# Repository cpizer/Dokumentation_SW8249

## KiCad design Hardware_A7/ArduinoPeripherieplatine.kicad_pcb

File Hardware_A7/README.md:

Diese Hardware ist in der Komponente die im Schaltplan A7 heisst installiert.

R4,R6,C3 mit circuitlab etwa auf 1kHz im timedomain eingestellt. R4
und R6 halbieren die Eingangsspannung von den angenommenen 40V auf
20V. Die negative Halbwelle fliest nur durch R4 und D6. Habe mit
maximal 40V gerechnet. Sind dann nur 70mW. also passt 1/8W
Widerstand. Die positive Halbwelle wird auf die 5V Schiene
geladen. Diese wird jedoch von der 2,5V Spannungsteilerschaltung so
stark belastet, dass auf keinen Fall rückgespeist wird.

Schmitttrigger R3 und R5 sind dimensioniert auf 3V ein, 2V
aus. Achtung, die OP-AMPS sind im nicht rail to rail!

teste dass der schmitt trigger ausreichend sicher an geht in den
extremlagen wiel die opamps ja nicht rail to rail sind. wenn nicht,
vergrößere R5.

Ohne R6 kann "Signal Licht" frei floaten. Der Widerstand verhindert
das.

D1 ist interessant, wenn die Versorgungsspannung fehlt. Man kann die
Versorgungsspannung jedoch nicht überhöhen, dagegen schützt D5.

D2 gibt die parasitäre Versorgung dann nach aussen weiter und schützt
U1.

C3 ist so dimensioniert dass 1 kHz Grenzfrequenz überschritten
werden. Weil das Original Arduino Programm mit der millis funktion die
Geschwindigkeiten bestimmt und diese maximal 1kHz aufgelöst sein kann.

R1 und R2 sind ein Spannungsteiler zur Erzeugung von 2,5V. Sie dienen
aber auch einer Grundlast um die parasitäre Erzeugung von 5V zu
unterbinden.

R7 ist der Stromshunt für den Kardansensor. Der Kardansensor soll 7mA
oder 14mA liefern. Also ist der Trennpunkt bei 10,5mA. Die Spannung
soll dabei 2,5V sein. Der nächste Widerstand ist dann 220Ohm. R7 soll
wenn er 12V direkt bekommt nicht durchbrennen. 654mW wäre
theoretisch. Daher ein 1W Widerstand. R8 und C6 sind ein
Tiefpass. Wieder eingestellt auf 1kHz Grenzfrequenz.

Auslegung des Schmitt Triggers U4D: 7mA bei 220 Ohm sind 1,54V. 14mA
bei 220 Ohm sind 3,08V. Den Bereich dazwischen dritteln ergibt die
zwei Schranken 2,05V und 2,57V. Mit dem Onlinetool berechnet:
R10=10k R9=1,5k

VD ist die spannung der mitte des 5V opamp ausgangs. also 0-3,5V also
1,75V. mit realen widerständen ist sie 1,85V

https://www.aaabbb.de/NonInvertingSchmittTrigger/NonInvertingSchmittTrigger_en.php

Bedenke den Stromverbrauch des Servos! Er kann die 5V
runterziehen. Mit dem alten defekten Servo der sich nicht mehr drehte
war die 5V Spannung auf 2,6V oder so zusammengebrochen und der Wandler
wurde heiss. Max Servostrom (des neuen nicht defekten Servos) ist
ca. 200mA. der 5V Linear Wandler wird nach einer Minute Servo
dauerlauf hot und regelt runter. Ist auch logisch bei 24V input. Habe
daher den Servopower entkoppelt mit einem Schaltregler.

Die Drehzahlanzeige hat einen Widerstand von 2,5kOhm.

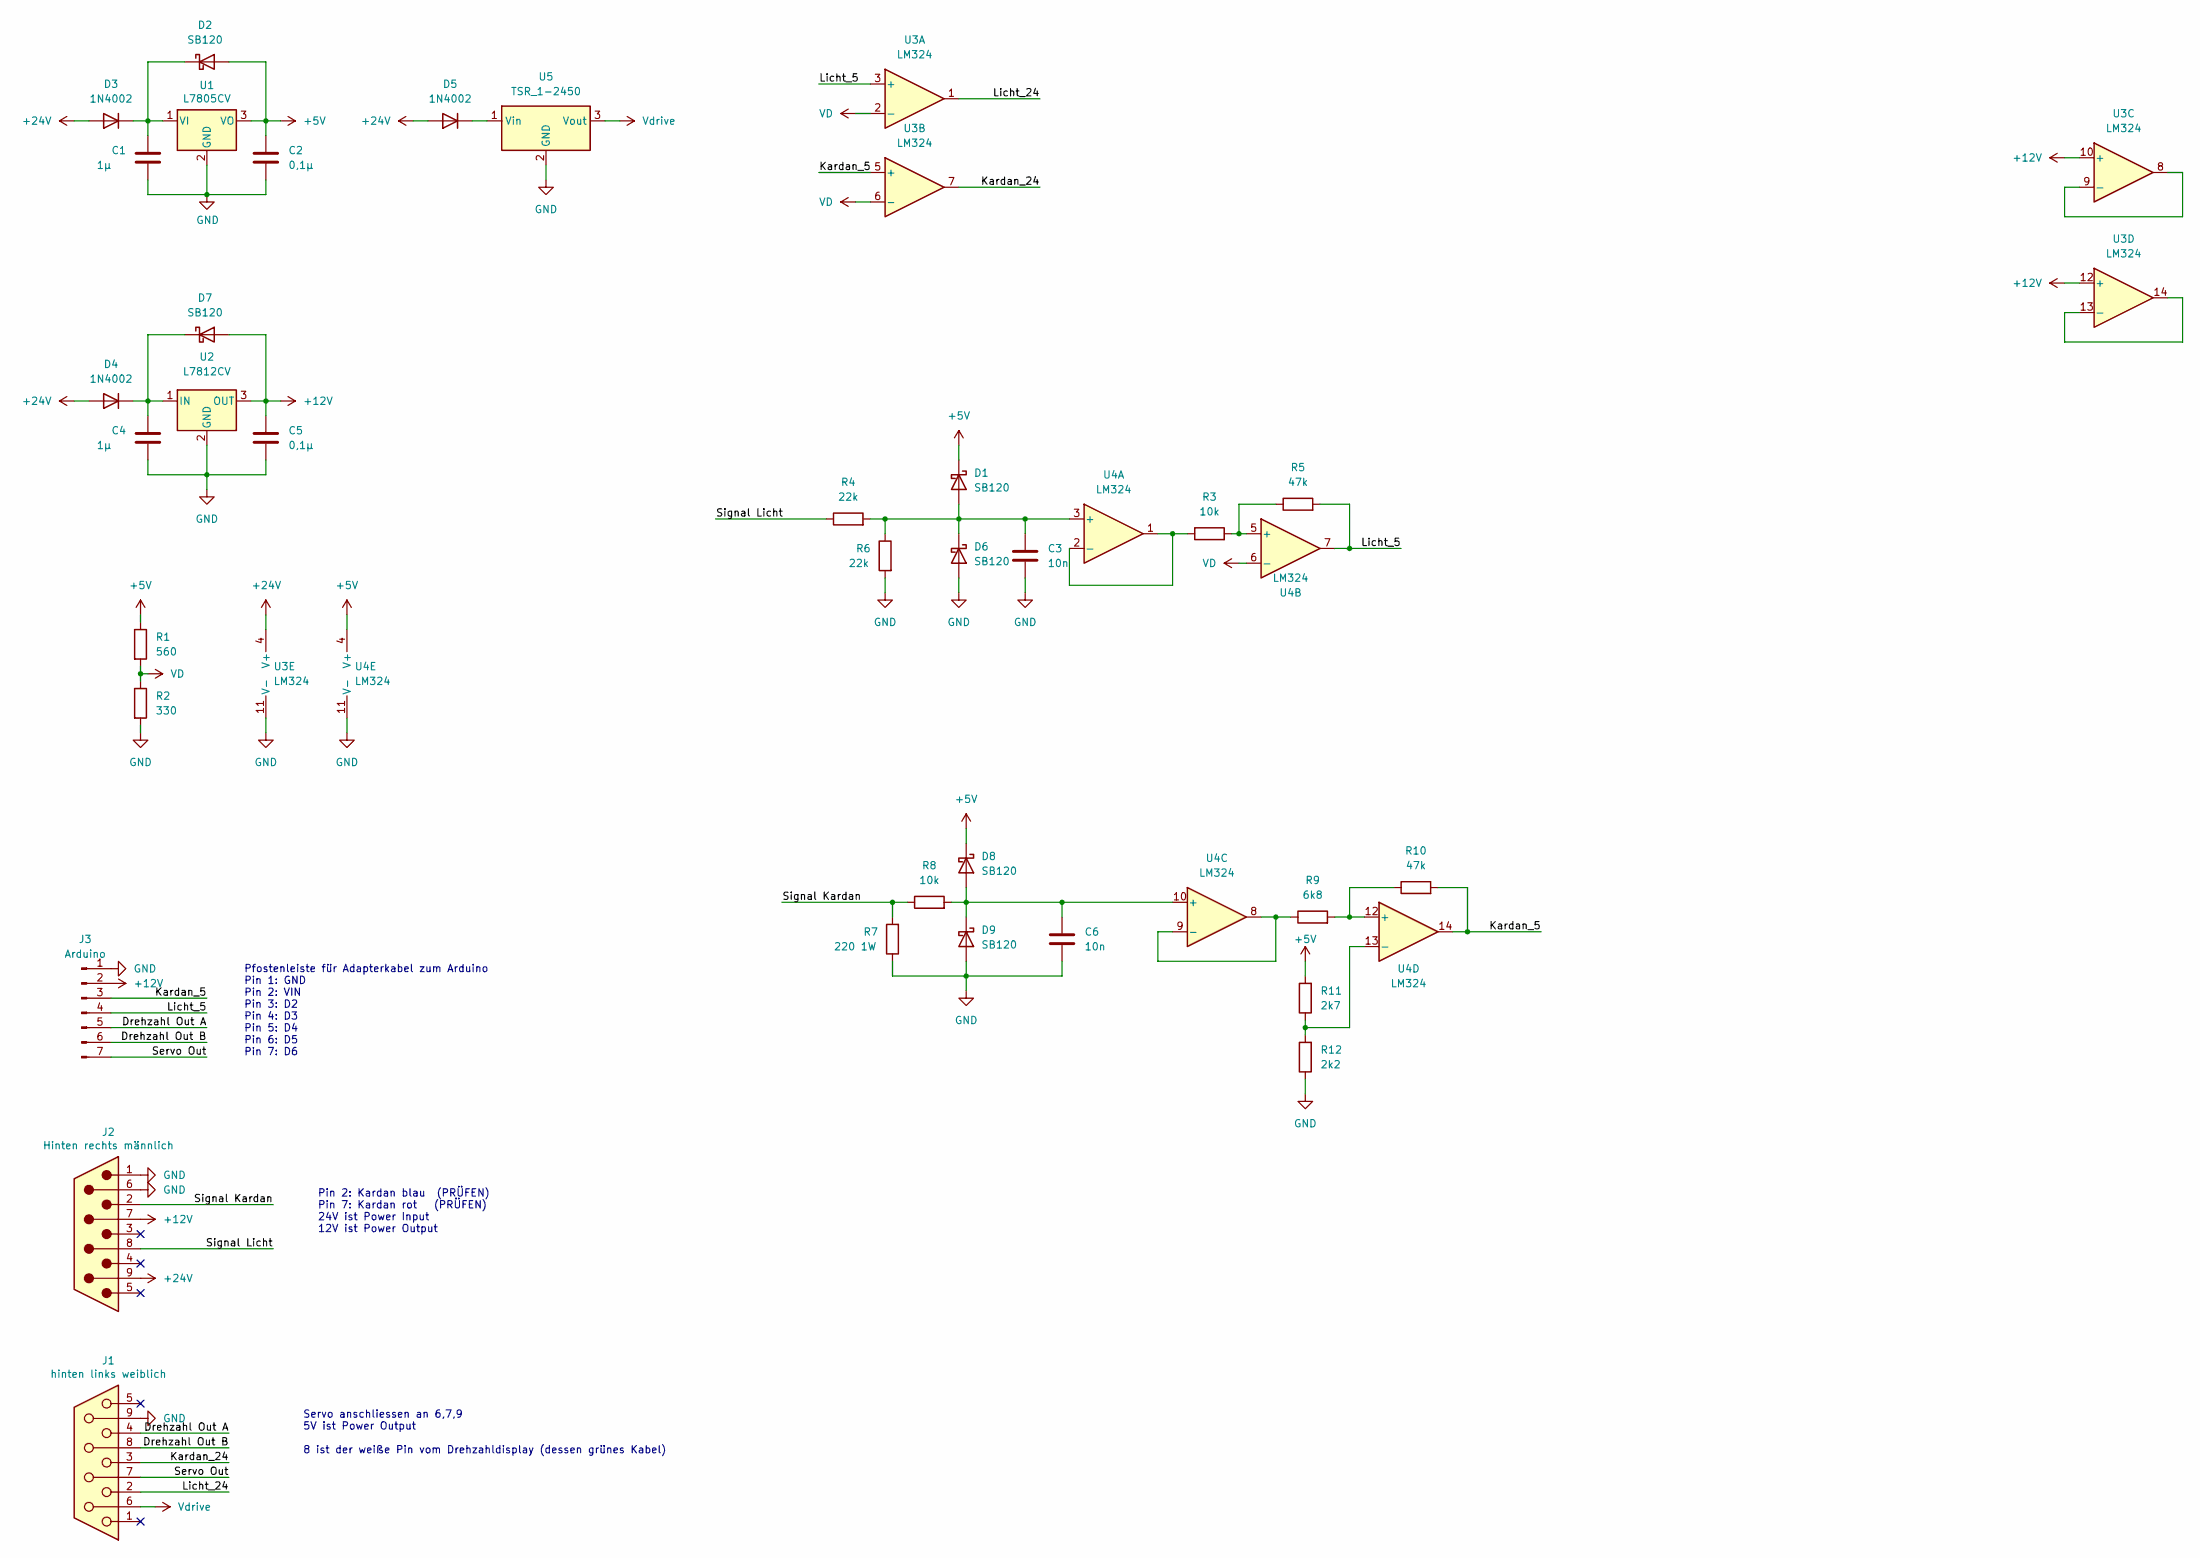
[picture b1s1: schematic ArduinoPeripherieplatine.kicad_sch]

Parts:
C1, C4: 1µ; C_Disc_D5.1mm_W3.2mm_P5.00mm
C2, C5: 0,1µ; C_Disc_D5.1mm_W3.2mm_P5.00mm
C3, C6: 10n; C_Disc_D9.0mm_W2.5mm_P5.00mm
D1, D2, D6, D7, D8, D9: SB120; D_DO-41_SOD81_P10.16mm_Horizontal
D3, D4, D5: 1N4002; D_DO-41_SOD81_P7.62mm_Horizontal
J1: hinten links weiblich; PinHeader_1x09_P2.54mm_Vertical
J2: Hinten rechts männlich; PinHeader_1x09_P2.54mm_Vertical
J3: Arduino; PinHeader_1x07_P2.54mm_Vertical
R1: 560; R_Axial_DIN0207_L6.3mm_D2.5mm_P10.16mm_Horizontal
R2: 330; R_Axial_DIN0207_L6.3mm_D2.5mm_P10.16mm_Horizontal
R3, R8: 10k; R_Axial_DIN0207_L6.3mm_D2.5mm_P10.16mm_Horizontal
R4, R6: 22k; R_Axial_DIN0207_L6.3mm_D2.5mm_P10.16mm_Horizontal
R5, R10: 47k; R_Axial_DIN0207_L6.3mm_D2.5mm_P10.16mm_Horizontal
R7: 220 1W; R_Axial_DIN0207_L6.3mm_D2.5mm_P10.16mm_Horizontal
R9: 6k8; R_Axial_DIN0207_L6.3mm_D2.5mm_P10.16mm_Horizontal
R11: 2k7; R_Axial_DIN0207_L6.3mm_D2.5mm_P10.16mm_Horizontal
R12: 2k2; R_Axial_DIN0207_L6.3mm_D2.5mm_P10.16mm_Horizontal
U1: L7805CV; TO-220-3_Vertical
U2: L7812CV; TO-220-3_Vertical
U3, U4: LM324; DIP-14_W7.62mm_LongPads
U5: TSR_1-2450; Converter_DCDC_TRACO_TSR-1_THT

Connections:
+5V: C2.1, D1.1 (K), D2.2 (A), D8.1 (K), R1.1, R11.2, U1.3 (VO), U4.4 (V+)
+12V: C5.1, D7.2 (A), J2.7, J3.2, U2.3 (OUT), U3.10 (+), U3.12 (+)
+24V: D3.2 (A), D4.2 (A), D5.2 (A), J2.9, U3.4 (V+)
/Drehzahl Out A: J1.4, J3.5
/Drehzahl Out B: J1.8, J3.6
/Kardan_5: J3.3, R10.2, U3.5 (+), U4.14
/Kardan_24: J1.3, U3.7
/Licht_5: J3.4, R5.2, U3.3 (+), U4.7
/Licht_24: J1.2, U3.1
/Servo Out: J1.7, J3.7
/Signal Kardan: J2.2, R7.2, R8.1
/Signal Licht: J2.8, R4.1
GND: C1.2, C2.2, C3.2, C4.1, C5.2, C6.2, D6.2 (A), D9.2 (A), J1.9, J2.1, J2.6, J3.1, R2.2, R6.2, R7.1, R12.1, U1.2 (GND), U2.2 (GND), U3.11 (V-), U4.11 (V-), U5.2 (GND)
unnamed: C1.1, D2.1 (K), D3.1 (K), U1.1 (VI)
unnamed: C3.1, D1.2 (A), D6.1 (K), R4.2, R6.1, U4.3 (+)
unnamed: C4.2, D4.1 (K), D7.1 (K), U2.1 (IN)
unnamed: C6.1, D8.2 (A), D9.1 (K), R8.2, U4.10 (+)
unnamed: D5.1 (K), U5.1 (Vin)
unnamed: R3.1, U4.1, U4.2 (-)
unnamed: R3.2, R5.1, U4.5 (+)
unnamed: R9.1, U4.8, U4.9 (-)
unnamed: R9.2, R10.1, U4.12 (+)
unnamed: R11.1, R12.2, U4.13 (-)
unnamed: U3.8, U3.9 (-)
unnamed: U3.13 (-), U3.14
VD: R1.2, R2.1, U3.2 (-), U3.6 (-), U4.6 (-)
Vdrive: J1.6, U5.3 (Vout)

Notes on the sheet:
Pfostenleiste für Adapterkabel zum Arduino Pin 1: GND Pin 2: VIN Pin 3: D2 Pin 4: D3 Pin 5: D4 Pin 6: D5 Pin 7: D6
Servo anschliessen an 6,7,9 5V ist Power Output 8 ist der weiße Pin vom Drehzahldisplay (dessen grünes Kabel)
Pin 2: Kardan blau (PRÜFEN) Pin 7: Kardan rot (PRÜFEN) 24V ist Power Input 12V ist Power Output

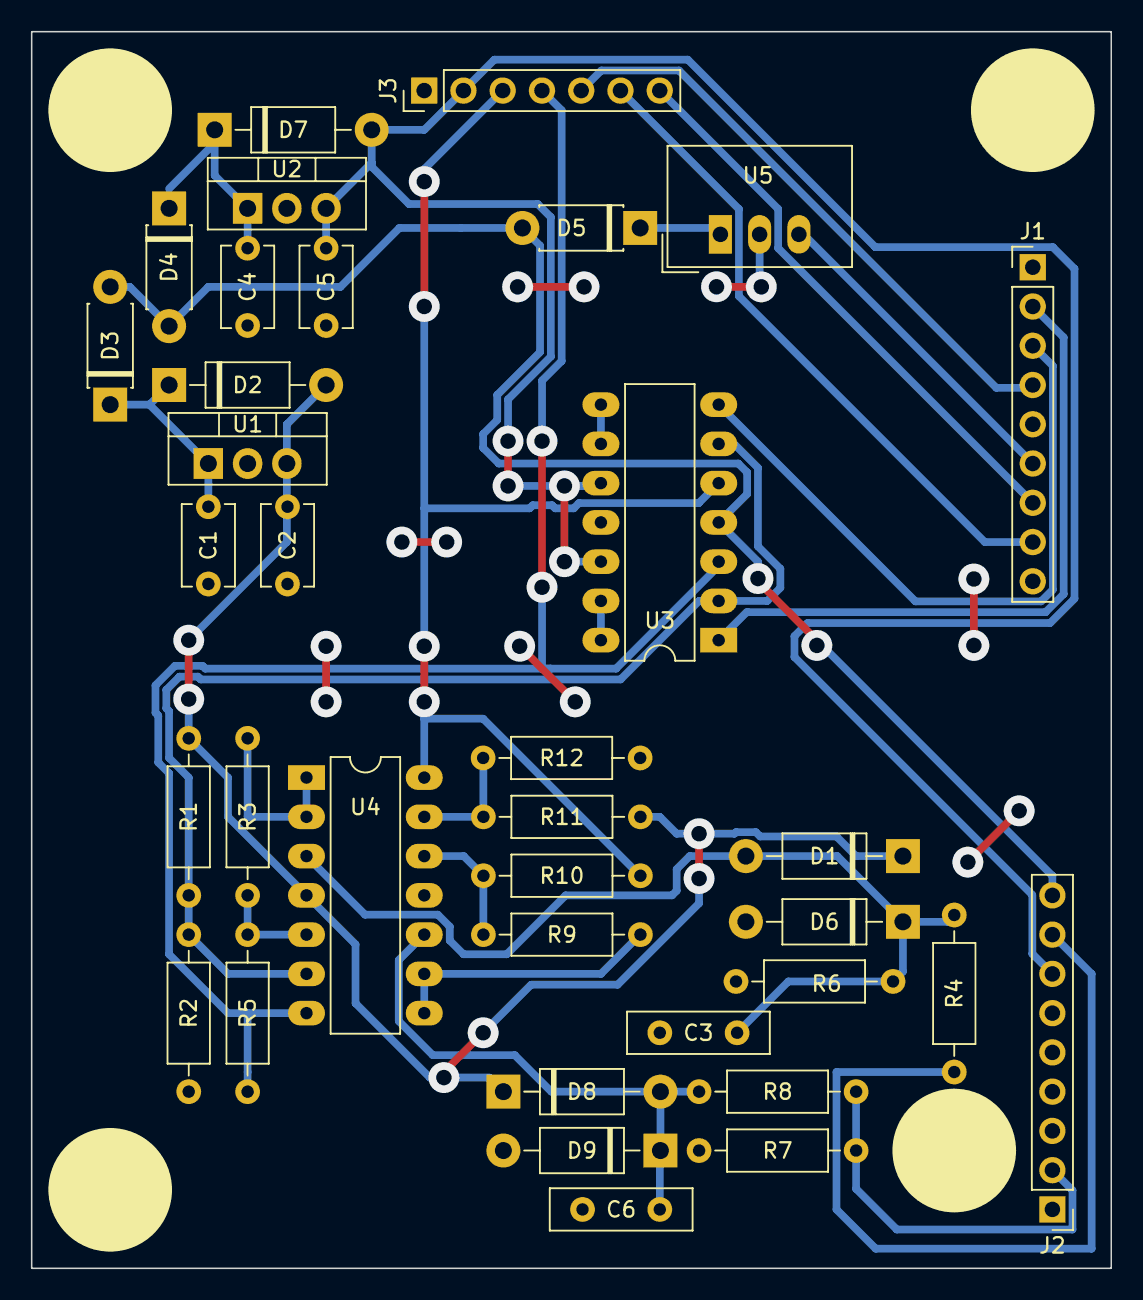
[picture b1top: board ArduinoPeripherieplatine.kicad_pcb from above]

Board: 2 copper layers, 69.9 x 80.0 mm, 35 parts (0 on the bottom side), 27 nets.

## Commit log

2022-05-27 Added Gauge Control Code to Repo
2022-07-23 Which_Gauge_Control Setup
2022-07-24 Updated .ini-file
2022-07-24 Implemented mean on rpm-pulses
2022-07-25 Added Schematic of Lichtmaschine-Signalaufbereitung PCB
2022-07-25 Added Laser Parts for Speedometer
2022-07-25 Abaenderung Arduino-Code fuer neuen Tacho
2022-07-25 CAD-Dateien strukturiert abgelegt
2022-07-26 Dokument Beschreibung Lichtmaschinenensignal erstellt
2022-07-30 Dokumentation Signalaufbereitung W-Klemme aktualisiert
2022-11-01 Updated Schematics of Signal Processing PCB
2022-11-08 Updated Peripheral PCB
2022-11-08 Updated Arduino Code
2022-11-09 Updated Arduino Code - Adjusted Constants
2023-03-19 Refactoring & Documentation
    -Refactored the Ardunio's Code controlling the cable-speed as well as the RPM-display
    -Updated the documentation of the electronic's box
2023-03-19 Updated Arduino code
    -Serial output optional now
    -Increased cable-speed-signal-buffer's size to make the measurement more robust
2023-03-19 Updated description of electronic's box
2023-03-19 Updated Documentation
2024-03-29 Version vor dem ersten Start
2024-04-07 initial
2024-04-09 Diese Version wurde Anfang 2024 in die Winde eingebaut.
2024-04-09 Header
2024-04-09 Altes demontiertes Zeug gelöscht. Mechanik angelegt.
2024-04-09 code gelöscht
2024-04-09 aufgeräumt
2024-04-11 Diese Version wurde Anfang 2024 eingebaut
2024-04-11 erste Version
2025-02-02 Rename IMG-20250122-WA0001.jpg to LKW/IMG-20250122-WA0001.jpg
2025-02-02 Rename q0011.png to Pneumatikplan.png
